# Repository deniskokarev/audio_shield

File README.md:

# STM32 Nucleo Audio Amplifier Shield

**A toy project for agentic development**

Exercises all stages or product prototyping:
- schematics
- SPICE simulation from CSV input into CSV (or WAV)
- schematics -> PCB

firmware:
- Zephyr POSIX DAC driver to capture DAC output stream into CSV
- Zephyr main that generates sound
- we can add virtual BLE capabilities with Aroid running in QEMU using Bumble

A compact, Arduino Uno R3-form-factor audio shield that amplifies the analog output of an MCU DAC. The board is designed around the STM32 NUCLEO-L476RG, using its `A2` header pin (`PA4`, DAC channel 1) as the audio source.

The current design is a single-channel (mono) output stage. It buffers the DAC signal with an OPA340 rail-to-rail op-amp, attenuates and AC-couples the signal into an LM386 audio power amplifier, and routes the amplified output through a coupling capacitor to a 3.5 mm jack.

## Features

- Arduino Uno R3 shield header layout for use with compatible STM32 Nucleo boards.
- `A2` / `PA4` / DAC channel 1 audio input on the intended NUCLEO-L476RG host.
- OPA340 unity-gain buffer to isolate the MCU DAC from the amplifier input network.
- LM386 audio power amplifier operating at its default gain of 20.
- 30 kOhm / 1 kOhm input attenuator.
- AC-coupled amplifier input and output.
- LM386 output stability network (50 nF in series with 10 Ohm to ground).
- Mono 3.5 mm audio output.
- 5 V operation from the Arduino-compatible power header.
- Two-layer PCB designed in KiCad 9.

## Signal Path

```text
STM32 DAC
A2 / PA4 / DAC1
      |
      v
OPA340 voltage follower
      |
      v
30 kOhm / 1 kOhm attenuator
      |
      v
10 uF input coupling capacitor
      |
      v
LM386 power amplifier (gain = 20)
      |
      v
10 uF output coupling capacitor
      |
      v
Mono 3.5 mm output jack
```

The OPA340 is powered from the shield's 5 V rail and is configured as a voltage follower. The LM386 gain-setting pins are left open, selecting the device's default voltage gain of 20. A 1 uF capacitor decouples the local supply.

## Board Compatibility

The shield uses the Arduino Uno R3 connector geometry, but electrical compatibility depends on the host board:

- **STM32 NUCLEO-L476RG:** the intended host. Its `A2` pin maps to `PA4`, which provides DAC channel 1.
- **Other Arduino-compatible Nucleo boards:** may work if they expose a true DAC output on `A2`, provide a compatible 5 V supply, and use the same header layout.
- **Classic Arduino Uno R3:** mechanically compatible with the header pattern, but its ATmega328P does not provide a true DAC on `A2`. PWM would require an appropriate reconstruction filter, or an external DAC would be needed.

The schematic also notes the NUCLEO-L476RG's second DAC channel on `A5` / `PA5`, but that pin is not connected in the current board. Only one audio channel is implemented.

## Output and Load Notes

The output connector uses a TRS-style physical footprint as a mono jack: the tip carries the amplified signal, the sleeve is ground, and the ring contact is unused.

The intended load impedance and target output power are not yet specified. The 10 uF output coupling capacitor produces a load-dependent low-frequency cutoff, so speaker, headphone, and line-level loads will behave differently. Verify output level, distortion, LM386 stability, and capacitor polarity with the intended load before treating the design as production-ready.

## Opening the Project

1. Open `audio_shield.kicad_pro` in KiCad 9 or a compatible newer release.
2. Open the schematic and PCB from the KiCad project manager.
3. Keep the project-local symbol and footprint libraries beside the project files so KiCad can resolve the custom Arduino shield symbol and footprint.
4. Run Electrical Rules Check (ERC) and Design Rules Check (DRC) before generating fabrication files.

## Project Files

| File or directory | Purpose |
|---|---|
| `README.md` | Project overview, hardware description, compatibility notes, and file inventory. |
| `audio_shield.kicad_pro` | Main KiCad project configuration, including schematic, PCB, ERC, DRC, routing, and text-variable settings. |
| `audio_shield.kicad_sch` | Schematic source containing the Arduino-compatible headers, OPA340 buffer, LM386 amplifier, passive components, output jack, net labels, and design notes. |
| `audio_shield.kicad_pcb` | PCB source containing the board outline, component placement, footprints, routed copper, vias, silkscreen, and copper zones. |
| `audio_shield.kicad_prl` | KiCad per-user project state, such as active layers, visibility, editor panels, and selection filters. It is not the authoritative circuit design. |
| `_ProjectSymbols.kicad_sym` | Project-local KiCad symbol library containing the custom Arduino Uno R3 shield/header symbol. |
| `_ProjectFootprints.pretty/` | Project-local KiCad footprint library directory. |
| `_ProjectFootprints.pretty/Arduino_Uno_R3_Square.kicad_mod` | Custom through-hole Arduino Uno R3 shield-header footprint with the connector geometry and reference graphics used by the PCB. |
| `sym-lib-table` | Maps the `_ProjectSymbols` nickname to the project-local symbol library. |
| `fp-lib-table` | Maps the `_ProjectFootprints` nickname to the project-local footprint library. |

## Current Scope

This repository contains the KiCad design sources and local libraries. It does not currently include firmware, a bill of materials, fabrication outputs, assembly drawings, measured performance data, or a license.

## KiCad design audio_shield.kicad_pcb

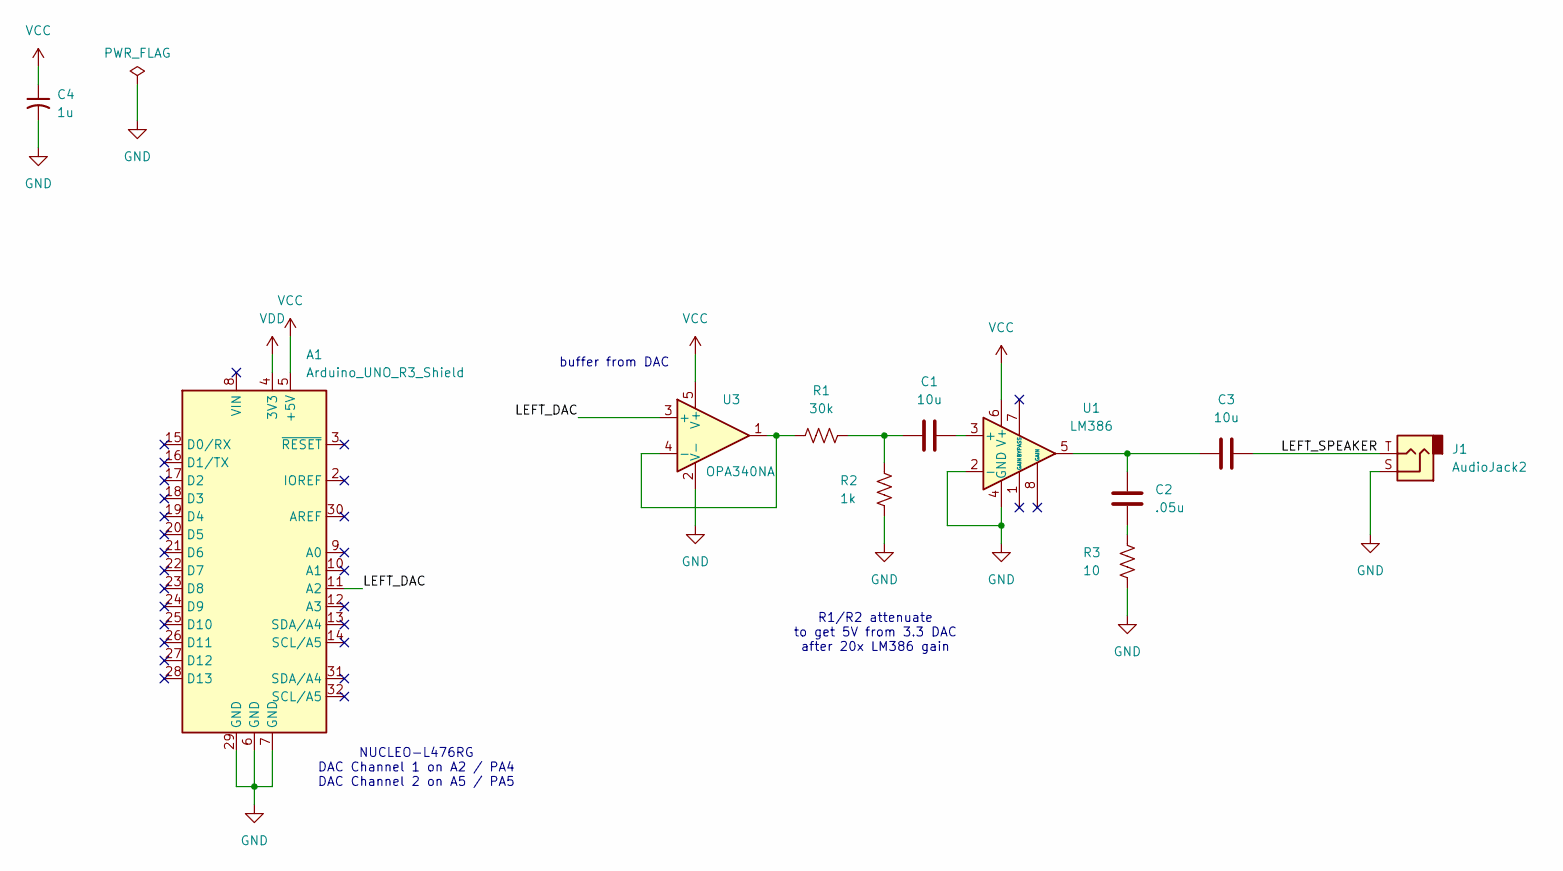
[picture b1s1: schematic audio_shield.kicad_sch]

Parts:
A1: Arduino_UNO_R3_Shield; Arduino_Uno_R3_Square
C1, C3: 10u; C_1206_3216Metric
C2: .05u; C_1206_3216Metric
C4: 1u; C_1206_3216Metric
J1: AudioJack2; Jack_3.5mm_CUI_SJ1-3513N_Horizontal
R1: 30k; R_1206_3216Metric
R2: 1k; R_1206_3216Metric
R3: 10; R_1206_3216Metric
U1: LM386; SOIC-8_3.9x4.9mm_P1.27mm
U3: OPA340NA; SOT-23-5

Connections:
/LEFT_DAC: A1.11 (A2), U3.3 (+)
/LEFT_SPEAKER: C3.1, J1.T
GND: A1.6 (GND), A1.7 (GND), A1.29 (GND), C4.2, J1.S, R2.2, R3.2, U1.2 (-), U1.4 (GND), U3.2 (V-)
unnamed: C1.1, R1.2, R2.1
unnamed: C2.1, R3.1
unnamed: C2.2, C3.2, U1.5
unnamed: C1.2, U1.3 (+)
unnamed: R1.1, U3.1, U3.4 (-)
VCC: A1.5 (+5V), C4.1, U1.6 (V+), U3.5 (V+)
VDD: A1.4 (3V3)

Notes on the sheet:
R1/R2 attenuate to get 5V from 3.3 DAC after 20x LM386 gain
buffer from DAC
NUCLEO-L476RG DAC Channel 1 on A2 / PA4 DAC Channel 2 on A5 / PA5

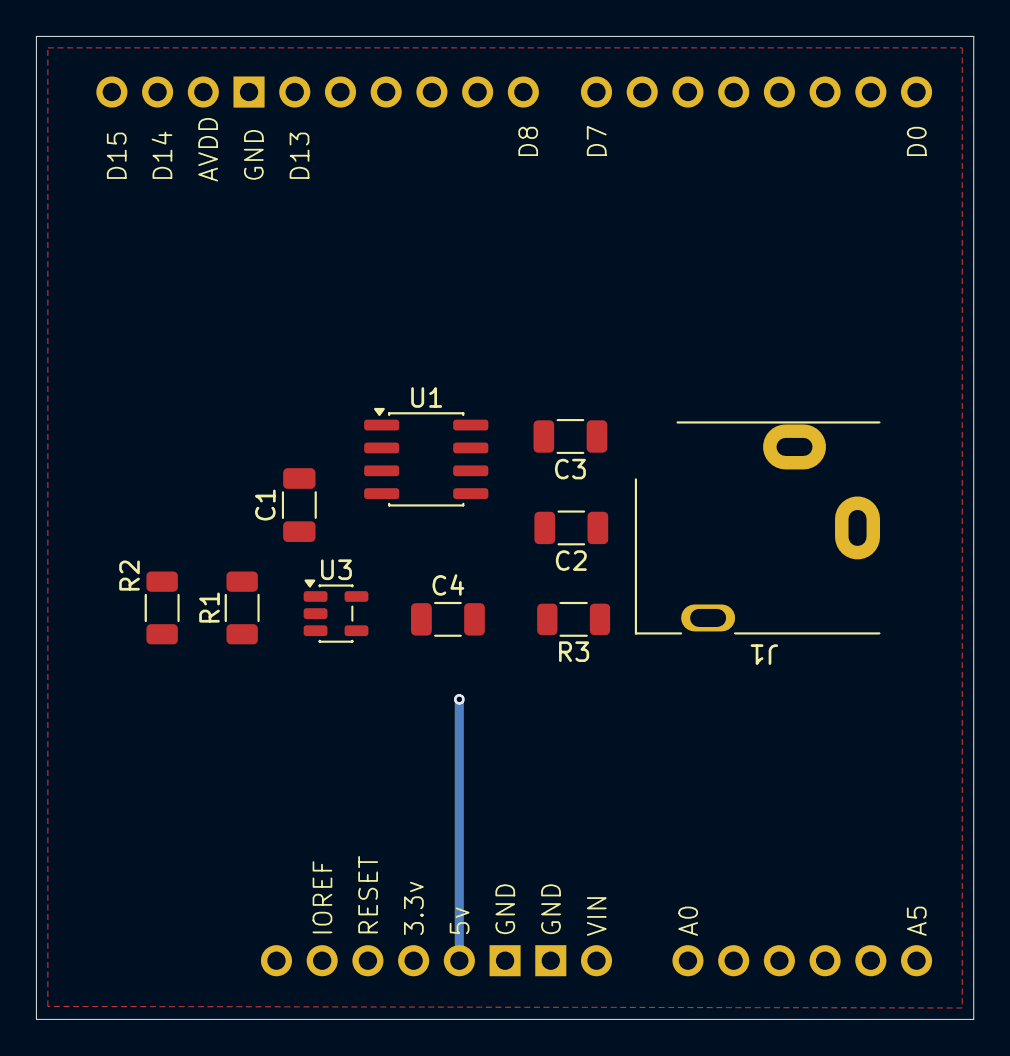
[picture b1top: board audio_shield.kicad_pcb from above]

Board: 2 copper layers, 52.1 x 54.6 mm, 11 parts (0 on the bottom side), 9 nets.
